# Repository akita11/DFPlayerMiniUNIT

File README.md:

# DFPlayerMiniUNIT

※当初掲載していた"DFPlayerMini"をとりつけた状態の写真で、DFPlayerMiniの向きが逆になっていました。こちらの写真が正しいです。

DFRobotの音声プレーヤモジュール[DFPlayer(DFPlayerMini)](https://www.switch-science.com/products/4291)をGrove端子を接続して制御できるモジュールです。Grove端子からシリアル(UART)通信で音声再生などを制御することができます。UIFlow(v1)用のブロックもあります。

※DFPlayerMiniは付属していません

## 使い方（接続方法）

以下のようにスピーカやアンプを接続し、Grove端子からの制御で音声を再生します。

### アンプ付きスピーカに接続する場合

3.5mmジャック（ステレオ：上部中央）に3.5mmステレオケーブル等でアンプに接続します。

### スピーカを直接接続する場合

基板中央部の1.25mmピッチコネクタ(Molex 53047-0210用)にスピーカを接続します。市販の小型スピーカ（M5Stack本体に使われているものなど。AliExpressやTaobaoでも同等品があります）を接続することができます。

※当初掲載していた"DFPlayerMini"をとりつけた状態の写真で、DFPlayerMiniの向きが逆になっていました。こちらの写真が正しいです。

### 3.5mmジャックに直接スピーカを接続する方法

3.5mmジャックに直接スピーカを接続することもできます。その場合は、基板裏面のハンダジャンパを以下のように修正してください。

- JP1をカット
- JP2・JP3の中央と△マーク側をカットし、中央と反対側（△マークがない側）をショート

## 使い方（ソフトウエア）

あらかじめ、microSDカードに使用する音声データ（*.mp3等）をコピーしておき、それをDFPlayerMiniにさしておきます。（このときコピーした順番が、再生時に使用する「曲番号」になります）

### UIFlow(v1)での使い方

「DFPlayerMini.m5b」をダウンロードし、UIFlow(v1)の"Custom"の"Open *.m5b"からこのファイルを指定すると、Init、Play、Volume、Stopの4つのブロックを使用できます。

- DFPlayerMini_Init : 初期化。最初に1回だけ読み出します。"TX"と"RX"には、使用するGroveポート・マイコン本体にあわせて、使用するピン番号を指定します。例えば、M5StackBasicのPortA（本体の赤いコネクタ）の場合は、上図のようにTX=21、RX=22を指定します。M5StackCore2のPortAの場合は、TX=32、RX=33となります。
- DFPlayerMini_Play : numに指定した「曲番号」の音声を再生します。
- DFPlayerMini_Volume : volに指定した音量に設定します。
- DFPlayerMini_Stop : 再生中の音声を停止します。

### その他のソフトウエアでの使い方

Arduino用にはライブラリがあるようなので、そちらを使ってもOKです。
あるいは、DFPlayerMiniのデータシート等を参考に、制御コマンドを送信して使用してください。

## Author

Junichi Akita (@akita11) / akita@ifdl.jp

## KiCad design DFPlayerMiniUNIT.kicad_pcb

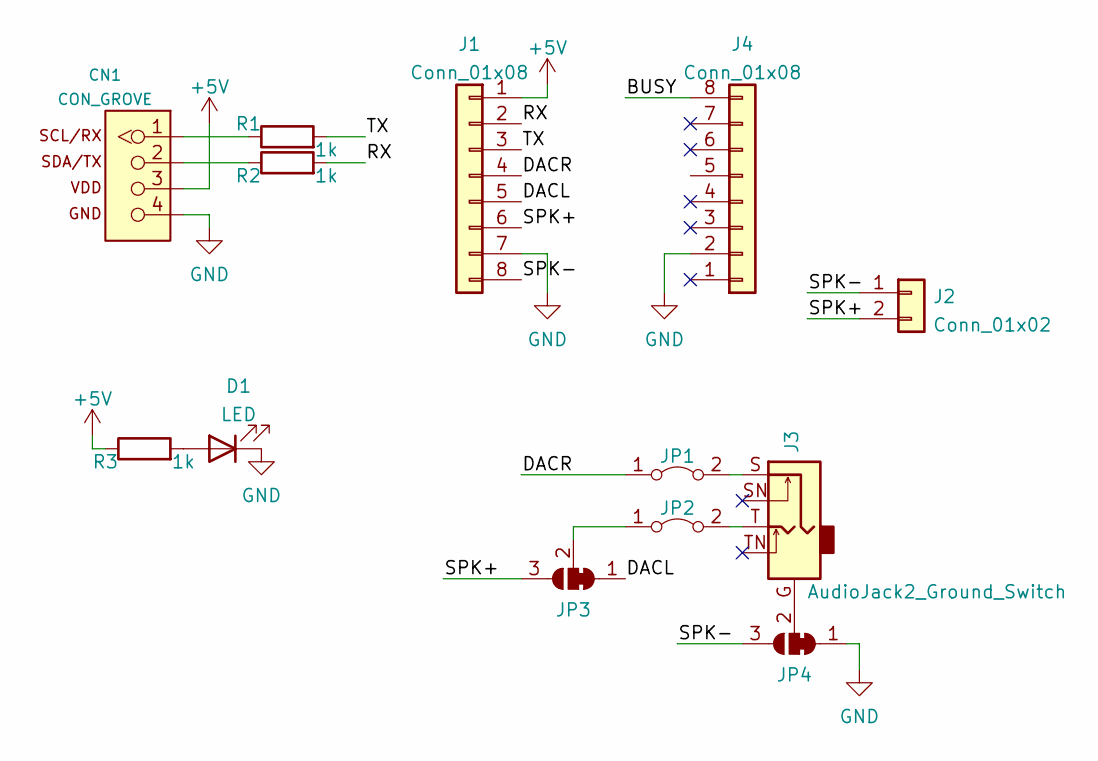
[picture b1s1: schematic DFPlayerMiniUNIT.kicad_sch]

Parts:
CN1: CON_GROVE; CON_GROVE_H
D1: LED; LED_0603_1608Metric
J1, J4: Conn_01x08; PinSocket_1x08_P2.54mm_Vertical
J2: Conn_01x02; Molex_PicoBlade_53047-0210_1x02_P1.25mm_Vertical
J3: AudioJack2_Ground_Switch; CON_AJ-1780
JP1, JP2: Jumper_2_Bridged; SolderJumper-2_P1.3mm_Bridged_Pad1.0x1.5mm
JP3, JP4: SolderJumper_3_Bridged12; SolderJumper-3_P1.3mm_Bridged12_Pad1.0x1.5mm
R1, R2, R3: 1k; R_0603_1608Metric

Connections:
+5V: CN1.3, J1.1, R3.1
/BUSY: J4.8
/DACL: J1.5, JP3.1 (A)
/DACR: J1.4, JP1.1 (A)
/RX: J1.2, R2.2
/SPK+: J1.6, J2.2, JP3.3 (B)
/SPK-: J1.8, J2.1, JP4.3 (B)
/TX: J1.3, R1.2
GND: CN1.4, D1.1 (K), J1.7, J4.2, JP4.1 (A)
unnamed: CN1.1, R1.1
unnamed: CN1.2, R2.1
unnamed: D1.2 (A), R3.2
unnamed: J3.G, JP4.2 (C)
unnamed: J3.S, JP1.2 (B)
unnamed: J3.T, JP2.2 (B)
unnamed: JP2.1 (A), JP3.2 (C)

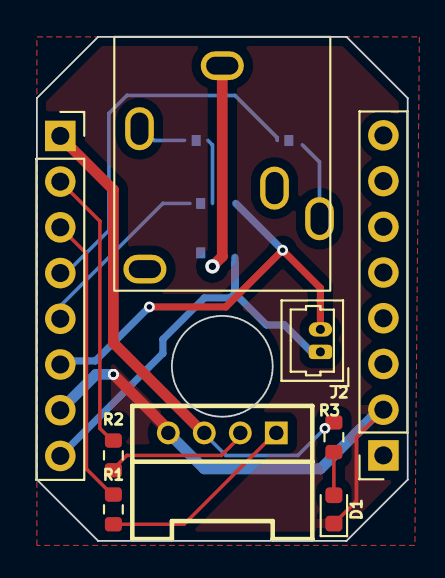
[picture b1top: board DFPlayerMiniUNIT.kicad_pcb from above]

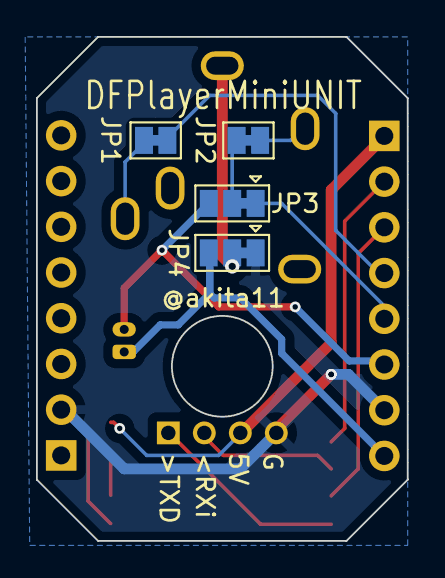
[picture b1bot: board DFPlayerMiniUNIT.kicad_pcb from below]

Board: 2 copper layers, 20.6 x 28.0 mm, 13 parts (4 on the bottom side), 15 nets.

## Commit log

2024-12-25 tentative, photo to be replaced
2025-01-02 add photo
2025-01-02 typo fix
2025-01-14 w/DFPlayerMini photo replace
2025-01-14 photo rename
2025-01-14 update photo
